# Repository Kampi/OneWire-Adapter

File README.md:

# 1-Wire Adapter

## Table of Contents

- [1-Wire Adapter](#1-wire-adapter)
  - [Table of Contents](#table-of-contents)
  - [About](#about)
  - [History](#history)
  - [Maintainer](#maintainer)

## About

Small extension board to use a UART as a 1-Wire interface.

## History

| **Version**  | **Description**                            | **Date**   |
|:------------:|:------------------------------------------:|:----------:|
| 1.0          | First hardware release                     | 30.09.2020 |

## Maintainer

- [Daniel Kampert](mailto:DanielKampert@kampis-elektroecke.de)

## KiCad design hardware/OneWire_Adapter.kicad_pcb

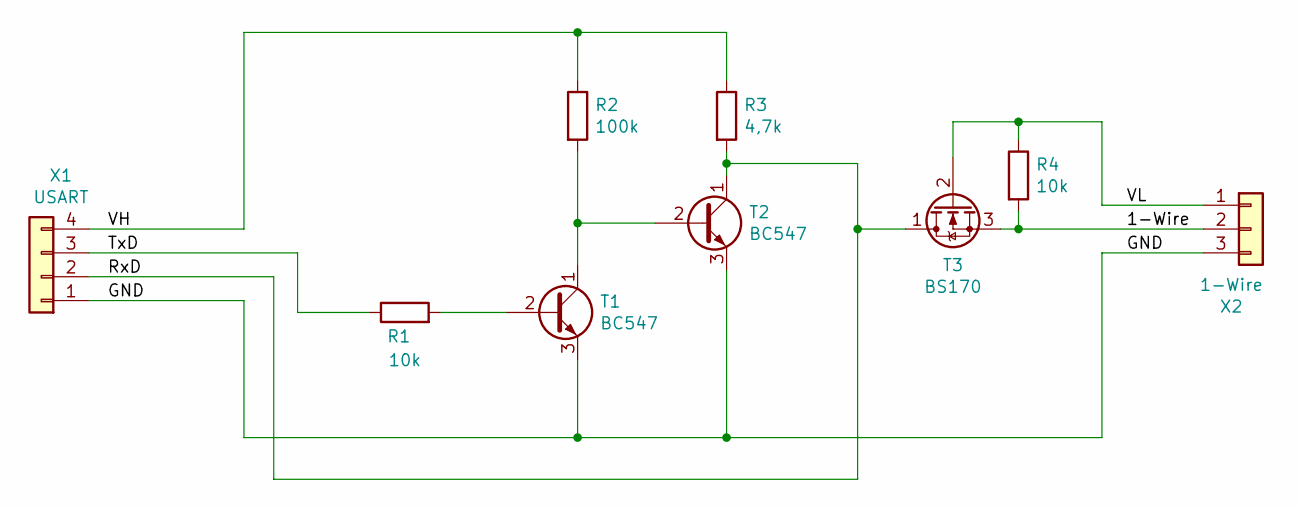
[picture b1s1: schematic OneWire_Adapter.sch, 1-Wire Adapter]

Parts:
R1, R4: 10k; R_Axial_DIN0207_L6.3mm_D2.5mm_P10.16mm_Horizontal; Mouser 603-MFR-25FBF52-10K
R2: 100k; R_Axial_DIN0207_L6.3mm_D2.5mm_P10.16mm_Horizontal; Mouser 603-MFR-25FBF52-100K
R3: 4,7k; R_Axial_DIN0207_L6.3mm_D2.5mm_P10.16mm_Horizontal; Mouser 603-MFR-25FBF52-4K7
T1, T2: BC547; TO-92_Inline; Mouser 512-BC547ATA
T3: BS170; TO-92_Inline; Mouser 512-BS170
X1: USART; PinHeader_1x04_P2.54mm_Horizontal; Mouser 855-M20-9770445
X2: 1-Wire; PinHeader_1x03_P2.54mm_Horizontal; Mouser 855-M20-9750346

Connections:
/1-Wire: R4.2, T3.3 (S), X2.2
/GND: T1.3 (E), T2.3 (E), X1.1, X2.3
/RxD: R3.2, T2.1 (C), T3.1 (D), X1.2
/TxD: R1.1, X1.3
/VH: R2.1, R3.1, X1.4
/VL: R4.1, T3.2 (G), X2.1
unnamed: R1.2, T1.2 (B)
unnamed: R2.2, T1.1 (C), T2.2 (B)

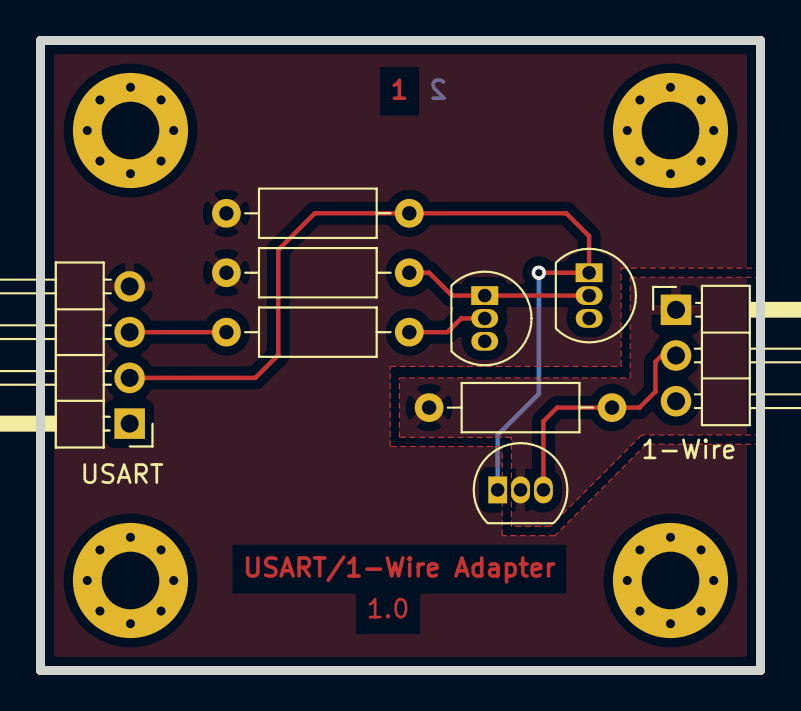
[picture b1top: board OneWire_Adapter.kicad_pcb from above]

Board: 2 copper layers, 40.0 x 35.0 mm, 9 parts (0 on the bottom side), 8 nets.

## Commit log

2020-01-29 First hardware version
2020-01-29 Typo in README
2020-01-29 Add level shifter
2020-01-30 Add production files
2020-01-30 Add new schematics
2020-02-09 Fix wrong email address in README
2020-02-13 Rename documents
2020-04-22 Update LICENSE
2020-09-30 Update project directory
2020-09-30 Rename project
